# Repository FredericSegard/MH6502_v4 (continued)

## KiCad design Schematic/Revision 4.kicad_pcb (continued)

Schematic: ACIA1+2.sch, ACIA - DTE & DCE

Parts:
C24, C25, C26, C27, C28, C29, C30, C31: 1µF; C_Disc_D3.0mm_W1.6mm_P2.50mm
C32, C33, C34, C35, C36: 0.1µF; C_Disc_D3.0mm_W1.6mm_P2.50mm
J12: DCE-F; DSUB-9_Female_Horizontal_P2.77x2.84mm_EdgePinOffset7.70mm_H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
J13: CTS; PinHeader_1x02_P2.54mm_Vertical
J14: RX; PinHeader_1x02_P2.54mm_Vertical
J15: SERIAL TTL; Mini-DIN_6p
J16: DTE-M; DSUB-9_Male_Horizontal_P2.77x2.84mm_EdgePinOffset7.70mm_Hou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
J17: SERIAL TTL; PinHeader_1x06_P2.54mm_Vertical
U12, U14: R65C51P2; DIP-28_W15.24mm_Socket
U13, U15: MAX232; DIP-16_W7.62mm_Socket
X3: 1.8432MHz; Oscillator_DIP-8

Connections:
+5V: C24.2, C28.2, C32.1, C33.1, C34.1, C35.1, C36.1, J15.4, J17.3, U12.2 (CS0), U12.15 (VCC), U13.16 (VCC), U14.2 (CS0), U14.15 (VCC), U15.16 (VCC), X3.1 (EN), X3.8 (Vcc); also elsewhere on the board
/ACIA/A0: U12.13 (RS0), U14.13 (RS0); also elsewhere on the board
/ACIA/A1: U12.14 (RS1), U14.14 (RS1); also elsewhere on the board
/ACIA/ACLK: U12.6 (XTLI), U14.6 (XTLI), X3.5 (OUT)
/ACIA/CTS: J13.1, J15.5, J17.2, U14.9 (~CTS)
/ACIA/D0: U12.18 (D0), U14.18 (D0); also elsewhere on the board
/ACIA/D1: U12.19 (D1), U14.19 (D1); also elsewhere on the board
/ACIA/D2: U12.20 (D2), U14.20 (D2); also elsewhere on the board
/ACIA/D3: U12.21 (D3), U14.21 (D3); also elsewhere on the board
/ACIA/D4: U12.22 (D4), U14.22 (D4); also elsewhere on the board
/ACIA/D5: U12.23 (D5), U14.23 (D5); also elsewhere on the board
/ACIA/D6: U12.24 (D6), U14.24 (D6); also elsewhere on the board
/ACIA/D7: U12.25 (D7), U14.25 (D7); also elsewhere on the board
/ACIA/RTS: J15.6, J17.6, U14.8 (~RTS), U15.10 (T2IN)
/ACIA/RX: J14.1, J15.1, J17.5, U14.12 (Rx_Data)
/ACIA/TX: J15.2, J17.4, U14.10 (Tx_Data), U15.11 (T1IN)
/CLK: U12.27 (PHI2), U14.27 (PHI2); also elsewhere on the board
/R~W: U12.28 (R/~W), U14.28 (R/~W); also elsewhere on the board
/~ACIA1: U12.3 (~CS1); also elsewhere on the board
/~ACIA2: U14.3 (~CS1); also elsewhere on the board
/~IRQ5: U12.26 (~IRQ); also elsewhere on the board
/~IRQ6: U14.26 (~IRQ); also elsewhere on the board
/~RESET: U12.4 (~RESET), U14.4 (~RESET); also elsewhere on the board
GND: C27.1, C31.1, C32.2, C33.2, C34.2, C35.2, C36.2, J12.5, J15.3, J16.5, J17.1, U12.1 (GND), U12.16 (~DCD), U12.17 (~DSR), U13.15 (GND), U14.1 (GND), U14.16 (~DCD), U14.17 (~DSR), U15.15 (GND), X3.4 (GND); also elsewhere on the board
unnamed: C24.1, U13.2 (VS+)
unnamed: C25.1, U13.1 (C1+)
unnamed: C25.2, U13.3 (C1-)
unnamed: C26.1, U13.4 (C2+)
unnamed: C26.2, U13.5 (C2-)
unnamed: C27.2, U13.6 (VS-)
unnamed: C28.1, U15.2 (VS+)
unnamed: C29.1, U15.1 (C1+)
unnamed: C29.2, U15.3 (C1-)
unnamed: C30.1, U15.4 (C2+)
unnamed: C30.2, U15.5 (C2-)
unnamed: C31.2, U15.6 (VS-)
unnamed: J12.2, U13.14 (T1OUT)
unnamed: J12.3, U13.13 (R1IN)
unnamed: J12.7, U13.8 (R2IN)
unnamed: J12.8, U13.7 (T2OUT)
unnamed: J13.2, U15.9 (R2OUT)
unnamed: J14.2, U15.12 (R1OUT)
unnamed: J16.2, U15.13 (R1IN)
unnamed: J16.3, U15.14 (T1OUT)
unnamed: J16.7, U15.7 (T2OUT)
unnamed: J16.8, U15.8 (R2IN)
unnamed: U12.8 (~RTS), U13.10 (T2IN)
unnamed: U12.9 (~CTS), U13.9 (R2OUT)
unnamed: U12.10 (Tx_Data), U13.11 (T1IN)
unnamed: U12.12 (Rx_Data), U13.12 (R1OUT)

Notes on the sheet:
RTS
CTS
DCE to Computer
DTE to Peripheral
Bypass capacitors

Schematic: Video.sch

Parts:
C37, C38: 16pF; C_Disc_D3.4mm_W2.1mm_P2.50mm
C39, C40, C41, C42, C43, C44, C45: 0.1µF; C_Disc_D3.0mm_W1.6mm_P2.50mm
FB1: Ferrite Bead; L_Axial_L5.3mm_D2.2mm_P10.16mm_Horizontal_Vishay_IM-1
J18: INT; PinHeader_1x03_P2.54mm_Vertical
J19: COMPOSITE; RCAJackCUI
Q1: PN2222; TO-92L_Inline_Wide
R2: 470Ω; R_Axial_DIN0207_L6.3mm_D2.5mm_P10.16mm_Horizontal
R3: 75Ω; R_Axial_DIN0207_L6.3mm_D2.5mm_P10.16mm_Horizontal
RV1: 1KΩ; Potentiometer_Bourns_3296W_Vertical
U10: 74HCT04; DIP-14_W7.62mm_Socket
U16: TMS9918A/28A; DIP-40_W15.24mm_Socket
U17, U19, U20: 74HCT574; DIP-20_W7.62mm_Socket
U18: 71256; DIP-28_W7.62mm_Socket
Y2: 10.738635MHz; Crystal_HC18-U_Vertical

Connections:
+5V: C39.1, C40.1, C41.1, C42.1, C43.1, C44.1, FB1.1, U10.14 (VCC), U16.33 (VCC), U17.20 (VCC), U18.28 (VCC), U19.20 (VCC), U20.20 (VCC); also elsewhere on the board
/ACIA/A0: U16.13 (MODE); also elsewhere on the board
/ACIA/D0: U16.17 (D7); also elsewhere on the board
/ACIA/D1: U16.18 (D6); also elsewhere on the board
/ACIA/D2: U16.19 (D5); also elsewhere on the board
/ACIA/D3: U16.20 (D4); also elsewhere on the board
/ACIA/D4: U16.21 (D3); also elsewhere on the board
/ACIA/D5: U16.22 (D2); also elsewhere on the board
/ACIA/D6: U16.23 (D1); also elsewhere on the board
/ACIA/D7: U16.24 (D0); also elsewhere on the board
/Video/AD0: U16.10 (AD0), U17.2 (D0), U19.2 (D0), U20.2 (D0)
/Video/AD1: U16.9 (AD1), U17.3 (D1), U19.3 (D1), U20.3 (D1)
/Video/AD2: U16.8 (AD2), U17.4 (D2), U19.4 (D2), U20.4 (D2)
/Video/AD3: U16.7 (AD3), U17.5 (D3), U19.5 (D3), U20.5 (D3)
/Video/AD4: U16.6 (AD4), U17.6 (D4), U19.6 (D4), U20.6 (D4)
/Video/AD5: U16.5 (AD5), U17.7 (D5), U19.7 (D5), U20.7 (D5)
/Video/AD6: U16.4 (AD6), U17.8 (D6), U19.8 (D6), U20.8 (D6)
/Video/AD7: U16.3 (AD7), U17.9 (D7), U19.9 (D7), U20.9 (D7)
/Video/COL: U10.12, U19.11 (Cp)
/Video/COMP: RV1.2, U16.36 (COMVID)
/Video/FB: C45.1, FB1.2, Q1.3 (C)
/Video/ROW: U10.4, U17.11 (Cp)
/Video/RY: Q1.2 (B), R2.1, RV1.1
/Video/VA0: U17.18 (Q1), U18.10 (A0)
/Video/VA1: U17.17 (Q2), U18.9 (A1)
/Video/VA2: U17.16 (Q3), U18.8 (A2)
/Video/VA3: U17.15 (Q4), U18.7 (A3)
/Video/VA4: U17.14 (Q5), U18.6 (A4)
/Video/VA5: U17.13 (Q6), U18.5 (A5)
/Video/VA6: U17.12 (Q7), U18.4 (A6)
/Video/VA7: U18.3 (A7), U19.18 (Q1)
/Video/VA8: U18.25 (A8), U19.17 (Q2)
/Video/VA9: U18.24 (A9), U19.16 (Q3)
/Video/VA10: U18.21 (A10), U19.15 (Q4)
/Video/VA11: U18.23 (A11), U19.14 (Q5)
/Video/VA12: U18.2 (A12), U19.13 (Q6)
/Video/VA13: U18.26 (A13), U19.12 (Q7)
/Video/VD0: U16.32 (RD0), U18.11 (Q0), U20.19 (Q0)
/Video/VD1: U16.31 (RD1), U18.12 (Q1), U20.18 (Q1)
/Video/VD2: U16.30 (RD2), U18.13 (Q2), U20.17 (Q2)
/Video/VD3: U16.29 (RD3), U18.15 (Q3), U20.16 (Q3)
/Video/VD4: U16.28 (RD4), U18.16 (Q4), U20.15 (Q4)
/Video/VD5: U16.27 (RD5), U18.17 (Q5), U20.14 (Q5)
/Video/VD6: U16.26 (RD6), U18.18 (Q6), U20.13 (Q6)
/Video/VD7: U16.25 (RD7), U18.19 (Q7), U20.12 (Q7)
/Video/VR~W: U10.1, U16.11 (R~W), U18.27 (~WE), U20.1 (OE)
/Video/V~R~W: U10.2, U18.22 (~OE), U20.11 (Cp)
/Video/Y: J19.2, Q1.1 (E), R3.1
/Video/~CAS: U10.9, U16.2 (~CAS), U18.20 (~CS)
/Video/~INT: J18.2, U16.16 (~INT)
/Video/~RAS: U10.3, U16.1 (~RAS)
/~IRQ1: J18.1; also elsewhere on the board
/~NMI: J18.3; also elsewhere on the board
/~RESET: U16.34 (~RESET); also elsewhere on the board
/~VDPCSR: U16.15 (~CSR); also elsewhere on the board
/~VDPCSW: U16.14 (~CSW); also elsewhere on the board
GND: C37.2, C38.2, C39.2, C40.2, C41.2, C42.2, C43.2, C44.2, C45.2, J19.1, R2.2, R3.2, U10.7 (GND), U16.12 (GND), U17.1 (OE), U17.10 (GND), U18.1 (A14), U18.14 (GND), U19.1 (OE), U19.10 (GND), U20.10 (GND); also elsewhere on the board
unnamed: C37.1, U16.39 (XTAL1), Y2.2
unnamed: C38.1, U16.40 (XTAL2), Y2.1
unnamed: U10.10, U10.13
unnamed: U10.8, U10.11

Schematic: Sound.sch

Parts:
C46: 1µF; C_Disc_D3.0mm_W1.6mm_P2.50mm
C47, C48, C49, C50: 0.1µF; C_Disc_D3.0mm_W1.6mm_P2.50mm
J20: MONO; RCAJackCUI
R4, R5, R6, R10: 3K3Ω; R_Axial_DIN0207_L6.3mm_D2.5mm_P10.16mm_Horizontal
R7, R8, R9, R11: 1KΩ; R_Axial_DIN0207_L6.3mm_D2.5mm_P10.16mm_Horizontal
U21, U22, U23, U24: AY-3-8910; DIP-40_W15.24mm_Socket

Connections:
+5V: C47.1, C48.1, C49.1, C50.1, U21.25 (A8), U21.28 (BC2), U21.40 (VCC), U22.25 (A8), U22.28 (BC2), U22.40 (VCC), U23.25 (A8), U23.28 (BC2), U23.40 (VCC), U24.25 (A8), U24.28 (BC2), U24.40 (VCC); also elsewhere on the board
/ACIA/D0: U21.37 (DA0), U22.37 (DA0), U23.37 (DA0), U24.37 (DA0); also elsewhere on the board
/ACIA/D1: U21.36 (DA1), U22.36 (DA1), U23.36 (DA1), U24.36 (DA1); also elsewhere on the board
/ACIA/D2: U21.35 (DA2), U22.35 (DA2), U23.35 (DA2), U24.35 (DA2); also elsewhere on the board
/ACIA/D3: U21.34 (DA3), U22.34 (DA3), U23.34 (DA3), U24.34 (DA3); also elsewhere on the board
/ACIA/D4: U21.33 (DA4), U22.33 (DA4), U23.33 (DA4), U24.33 (DA4); also elsewhere on the board
/ACIA/D5: U21.32 (DA5), U22.32 (DA5), U23.32 (DA5), U24.32 (DA5); also elsewhere on the board
/ACIA/D6: U21.31 (DA6), U22.31 (DA6), U23.31 (DA6), U24.31 (DA6); also elsewhere on the board
/ACIA/D7: U21.30 (DA7), U22.30 (DA7), U23.30 (DA7), U24.30 (DA7); also elsewhere on the board
/BC1: U21.29 (BC1); also elsewhere on the board
/BC2: U22.29 (BC1); also elsewhere on the board
/BC3: U23.29 (BC1); also elsewhere on the board
/BC4: U24.29 (BC1); also elsewhere on the board
/BDIR1: U21.27 (BDIR); also elsewhere on the board
/BDIR2: U22.27 (BDIR); also elsewhere on the board
/BDIR3: U23.27 (BDIR); also elsewhere on the board
/BDIR4: U24.27 (BDIR); also elsewhere on the board
/PSG_CLK: U21.22 (CLK), U22.22 (CLK), U23.22 (CLK), U24.22 (CLK); also elsewhere on the board
/Sound/MONO: C46.2, R4.2, R5.2, R6.2, R10.2
/~RESET: U21.23 (~RESET), U22.23 (~RESET), U23.23 (~RESET), U24.23 (~RESET); also elsewhere on the board
GND: C47.2, C48.2, C49.2, C50.2, J20.1, R7.1, R8.1, R9.1, R11.1, U21.1 (GND), U21.24 (~A9), U22.1 (GND), U22.24 (~A9), U23.1 (GND), U23.24 (~A9), U24.1 (GND), U24.24 (~A9); also elsewhere on the board
unnamed: C46.1, J20.2
unnamed: R4.1, R7.2, U21.3 (CH_B), U21.4 (CH_A), U21.38 (CH_C)
unnamed: R5.1, R8.2, U22.3 (CH_B), U22.4 (CH_A), U22.38 (CH_C)
unnamed: R6.1, R9.2, U23.3 (CH_B), U23.4 (CH_A), U23.38 (CH_C)
unnamed: R10.1, R11.2, U24.3 (CH_B), U24.4 (CH_A), U24.38 (CH_C)

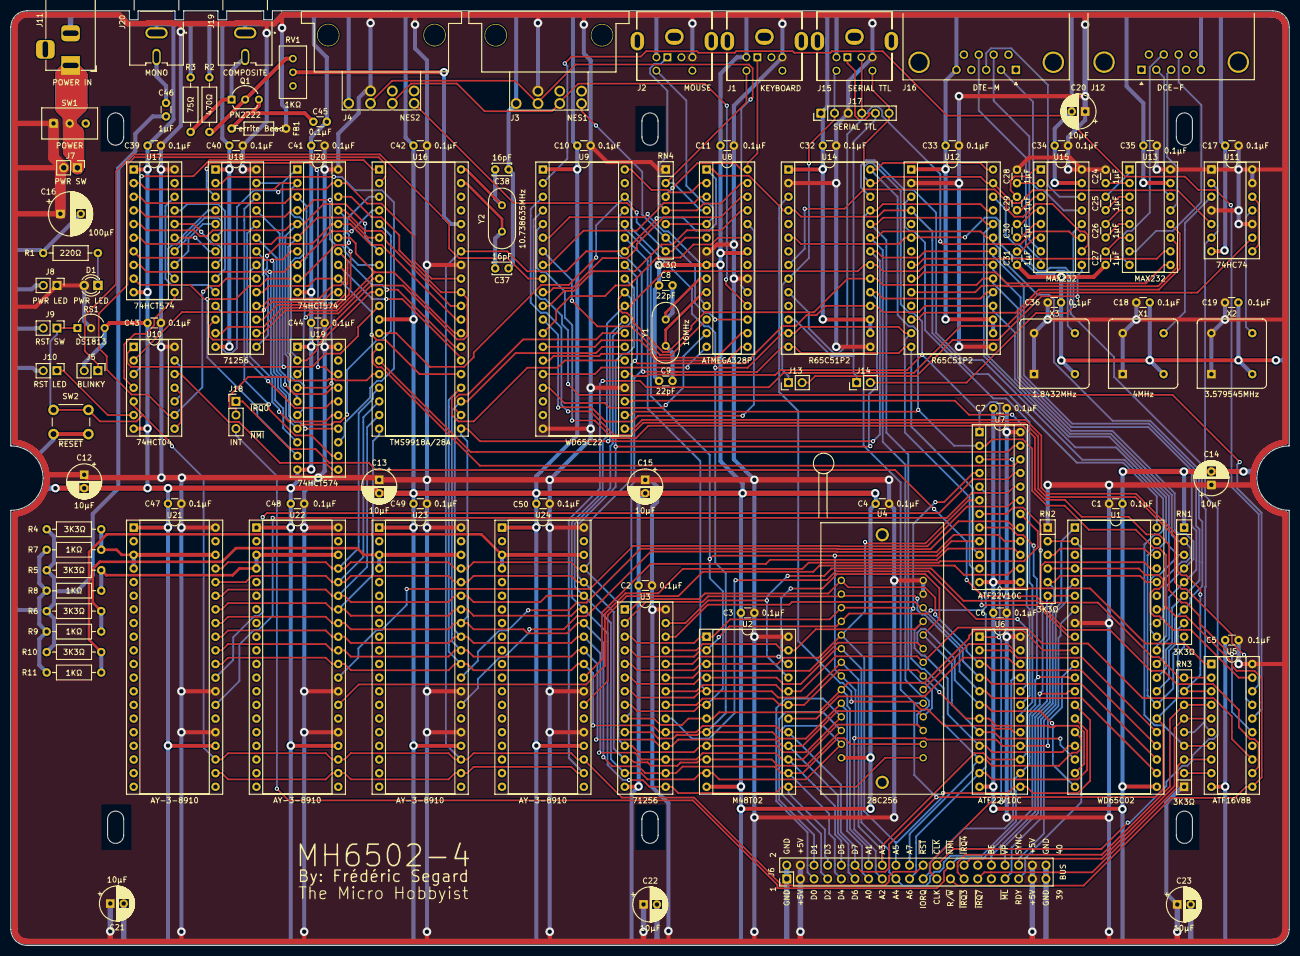
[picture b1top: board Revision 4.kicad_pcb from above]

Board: 2 copper layers, 238.0 x 174.0 mm, 121 parts (0 on the bottom side), 181 nets.

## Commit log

2023-08-16 Properly pushing my old 6502 project to GitHub
